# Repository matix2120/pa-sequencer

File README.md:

# pa-sequencer
Tiny board to key RF ampilifiers and LNAs

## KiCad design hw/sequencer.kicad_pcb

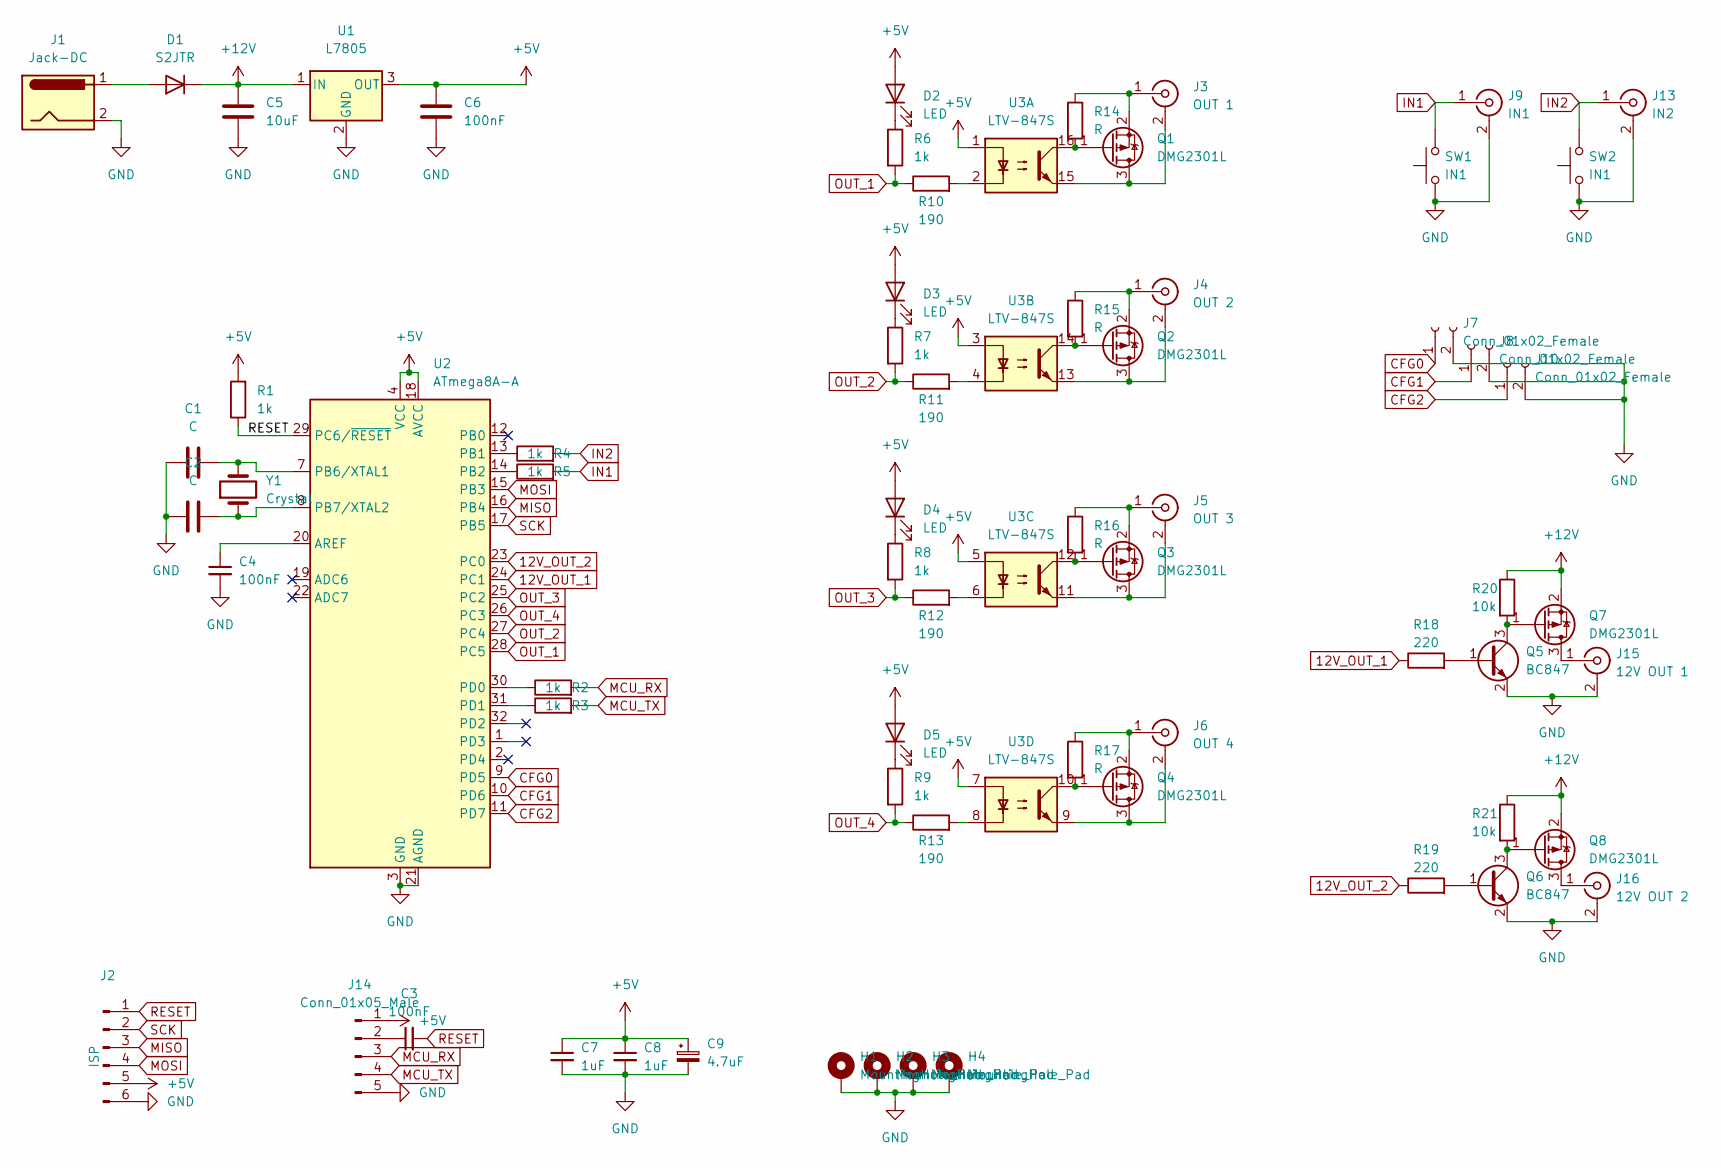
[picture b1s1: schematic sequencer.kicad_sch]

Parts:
C1, C2: C; C_0805_2012Metric_Pad1.18x1.45mm_HandSolder
C3, C4, C6: 100nF; C_0805_2012Metric_Pad1.18x1.45mm_HandSolder
C5: 10uF; C_0805_2012Metric_Pad1.18x1.45mm_HandSolder
C7, C8: 1uF; C_0805_2012Metric_Pad1.18x1.45mm_HandSolder
C9: 4.7uF; CP_Elec_4x4.5
D1: S2JTR; D_SMB
D2, D3, D4, D5: LED; LED_0805_2012Metric_Pad1.15x1.40mm_HandSolder
H1, H2, H3, H4: MountingHole_Pad; MountingHole_3.2mm_M3_Pad
J1: Jack-DC; PinHeader_1x02_P2.54mm_Vertical
J2: ISP; PinHeader_1x06_P2.54mm_Vertical
J3: OUT 1; PinHeader_1x02_P2.54mm_Vertical
J4: OUT 2; PinHeader_1x02_P2.54mm_Vertical
J5: OUT 3; PinHeader_1x02_P2.54mm_Vertical
J6: OUT 4; PinHeader_1x02_P2.54mm_Vertical
J7, J8, J10: Conn_01x02_Female; PinHeader_1x02_P2.54mm_Vertical
J9: IN1; PinHeader_1x02_P2.54mm_Vertical
J13: IN2; PinHeader_1x02_P2.54mm_Vertical
J14: Conn_01x05_Male; PinHeader_1x05_P2.54mm_Vertical
J15: 12V OUT 1; PinHeader_1x02_P2.54mm_Vertical
J16: 12V OUT 2; PinHeader_1x02_P2.54mm_Vertical
Q1, Q2, Q3, Q4, Q7, Q8: DMG2301L; SOT-23
Q5, Q6: BC847; SOT-23
R1, R2, R3, R4, R5, R6, R7, R8, R9: 1k; R_0805_2012Metric_Pad1.20x1.40mm_HandSolder
R10, R11, R12, R13: 190; R_0805_2012Metric_Pad1.20x1.40mm_HandSolder
R14, R15, R16, R17: R; R_0805_2012Metric_Pad1.20x1.40mm_HandSolder
R18, R19: 220; R_0805_2012Metric_Pad1.20x1.40mm_HandSolder
R20, R21: 10k; R_0805_2012Metric_Pad1.20x1.40mm_HandSolder
SW1, SW2: IN1; PTS636_SL43_SMTR_LFS
U1: L7805; TO-252-2
U2: ATmega8A-A; TQFP-32_7x7mm_P0.8mm
U3: LTV-847S; SMDIP-16_W9.53mm
Y1: Crystal; Crystal_SMD_HC49-SD

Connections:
12V_OUT_1: R18.1, U2.24 (PC1)
12V_OUT_2: R19.1, U2.23 (PC0)
+5V: C6.1, C7.1, C8.1, C9.1, D2.2 (A), D3.2 (A), D4.2 (A), D5.2 (A), J2.5, J14.1, R1.2, U1.3 (OUT), U2.4 (VCC), U2.6 (VCC), U2.18 (AVCC), U3.1, U3.3, U3.5, U3.7
+12V: C5.1, D1.1 (K), Q7.2 (S), Q8.2 (S), R20.1, R21.1, U1.1 (IN)
CFG0: J7.1, U2.9 (PD5)
CFG1: J8.1, U2.10 (PD6)
CFG2: J10.1, U2.11 (PD7)
GND: C1.2, C2.2, C4.2, C5.2, C6.2, C7.2, C8.2, C9.2, H1.1, H2.1, H3.1, H4.1, J1.2, J2.6, J7.2, J8.2, J9.2 (Ext), J10.2, J13.2 (Ext), J14.5, J15.2 (Ext), J16.2 (Ext), Q5.2 (E), Q6.2 (E), SW1.1, SW2.1, U1.2 (GND), U2.3 (GND), U2.5 (GND), U2.21 (AGND)
IN1: J9.1 (In), R5.2, SW1.2
IN2: J13.1 (In), R4.2, SW2.2
MCU_RX: J14.3, R2.2
MCU_TX: J14.4, R3.2
MISO: J2.3, U2.16 (PB4)
MOSI: J2.4, U2.15 (PB3)
unnamed: C1.1, U2.7 (PB6/XTAL1), Y1.2
unnamed: C2.1, U2.8 (PB7/XTAL2), Y1.1
unnamed: C4.1, U2.20 (AREF)
unnamed: D1.2 (A), J1.1
unnamed: D2.1 (K), R6.1
unnamed: D3.1 (K), R7.1
unnamed: D4.1 (K), R8.1
unnamed: D5.1 (K), R9.1
unnamed: J3.2 (Ext), Q1.3 (D), U3.15
unnamed: J4.1 (In), Q2.2 (S), R15.1
unnamed: J5.1 (In), Q3.2 (S), R16.1
unnamed: J6.1 (In), Q4.2 (S), R17.1
unnamed: C3.1, J14.2
unnamed: J15.1 (In), Q7.3 (D)
unnamed: J16.1 (In), Q8.3 (D)
unnamed: Q5.1 (B), R18.2
unnamed: Q5.3 (C), Q7.1 (G), R20.2
unnamed: Q6.1 (B), R19.2
unnamed: Q6.3 (C), Q8.1 (G), R21.2
unnamed: R2.1, U2.30 (PD0)
unnamed: R3.1, U2.31 (PD1)
unnamed: R10.2, U3.2
unnamed: R11.2, U3.4
unnamed: R12.2, U3.6
unnamed: R13.2, U3.8
unnamed: J3.1 (In), Q1.2 (S), R14.1
unnamed: Q1.1 (G), R14.2, U3.16
unnamed: R4.1, U2.13 (PB1)
unnamed: R5.1, U2.14 (PB2)
unnamed: J6.2 (Ext), Q4.3 (D), U3.9
unnamed: Q4.1 (G), R17.2, U3.10
unnamed: J5.2 (Ext), Q3.3 (D), U3.11
unnamed: Q3.1 (G), R16.2, U3.12
unnamed: J4.2 (Ext), Q2.3 (D), U3.13
unnamed: Q2.1 (G), R15.2, U3.14
OUT_1: R6.2, R10.1, U2.28 (PC5)
OUT_2: R7.2, R11.1, U2.27 (PC4)
OUT_3: R8.2, R12.1, U2.25 (PC2)
OUT_4: R9.2, R13.1, U2.26 (PC3)
RESET: C3.2, J2.1, R1.1, U2.29 (PC6/~RESET)
SCK: J2.2, U2.17 (PB5)

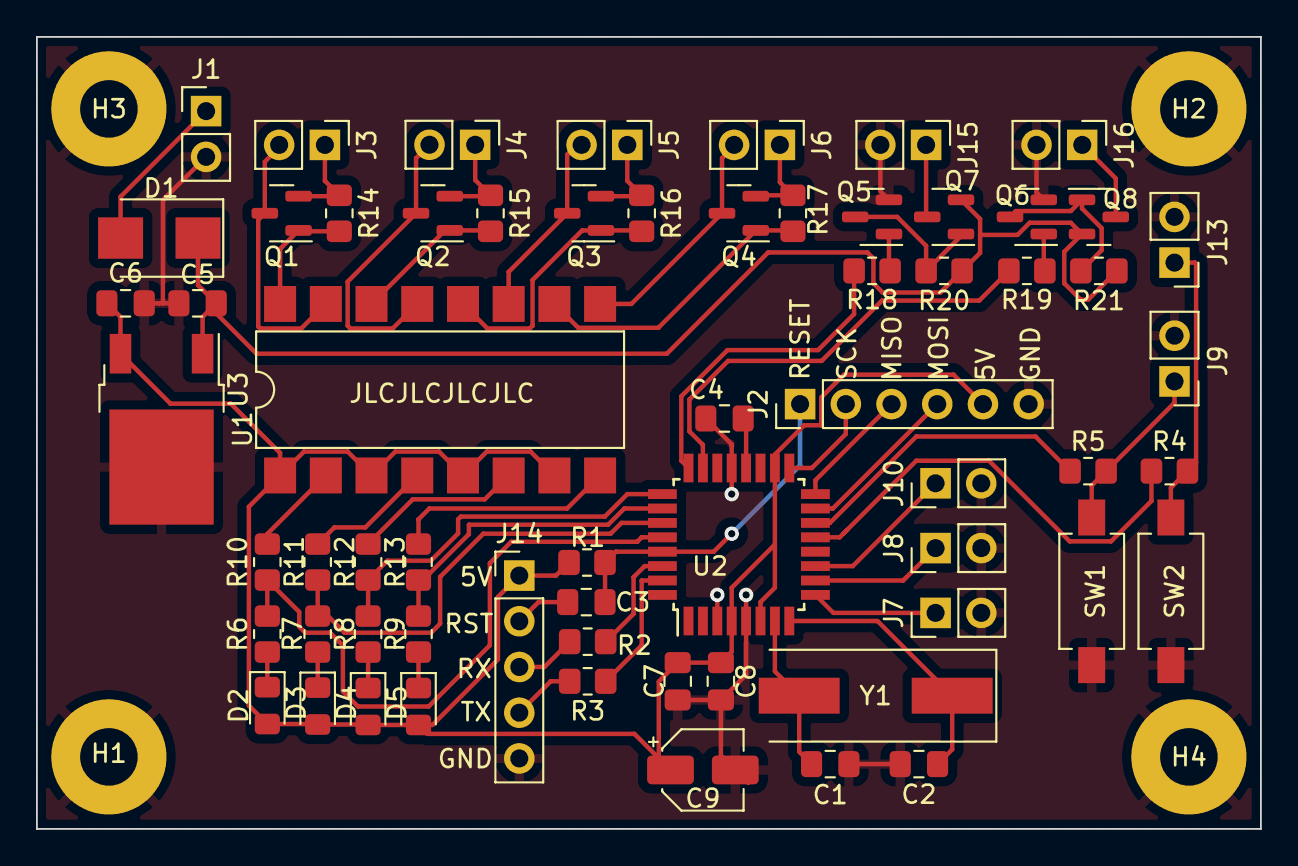
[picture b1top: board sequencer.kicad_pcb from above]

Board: 2 copper layers, 68.0 x 44.0 mm, 67 parts (0 on the bottom side), 55 nets.

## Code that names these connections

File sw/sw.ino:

#define IN1 PIN_PB2
#define IN2 PIN_PB1
#define OUT1 PIN_PC5
#define OUT2 PIN_PC4
#define OUT3 PIN_PC2
#define OUT4 PIN_PC3
#define OUT1_12V PIN_PC1
#define OUT2_12V PIN_PC0

#define OUT_ON(pin) digitalWrite(pin, LOW)
#define OUT_OFF(pin) digitalWrite(pin, HIGH)

#define OUT_12V_ON(pin) digitalWrite(pin, HIGH)
#define OUT_12V_OFF(pin) digitalWrite(pin, LOW)

#define PTT_ON(pin) !digitalRead(pin)

void setup() {
  Serial.begin(115200);
  Serial.println("PA Sequencer 2022");

  pinMode(IN1, INPUT_PULLUP);
  pinMode(IN2, INPUT_PULLUP);
  pinMode(OUT1, OUTPUT);
  pinMode(OUT2, OUTPUT);
  pinMode(OUT3, OUTPUT);
  pinMode(OUT4, OUTPUT);
  pinMode(OUT1_12V, OUTPUT);
  pinMode(OUT2_12V, OUTPUT);

  OUT_OFF(OUT1);
  OUT_OFF(OUT2);
  OUT_OFF(OUT3);
  OUT_OFF(OUT4);
  OUT_12V_OFF(OUT1_12V);
  OUT_12V_OFF(OUT2_12V);
}

void loop() {
  if(PTT_ON(IN1) || PTT_ON(IN2))
  {
    OUT_12V_OFF(OUT1_12V);
    OUT_12V_OFF(OUT2_12V);
    OUT_ON(OUT1);
    OUT_ON(OUT2);
    OUT_ON(OUT3);
    OUT_ON(OUT4);
  }
  else
  {
    OUT_12V_ON(OUT1_12V);
    OUT_12V_ON(OUT2_12V);
    OUT_OFF(OUT1);
    OUT_OFF(OUT2);
    OUT_OFF(OUT3);
    OUT_OFF(OUT4);
  }

//  Serial.print(digitalRead(OUT1));
//  Serial.print(",");
//  Serial.print(digitalRead(OUT2));
//  Serial.print(",");
//  Serial.print(digitalRead(OUT3));
//  Serial.print(",");
//  Serial.print(digitalRead(OUT4));
//  Serial.print(",");
//  Serial.print(digitalRead(OUT1_12V));
//  Serial.print(",");
//  Serial.println(digitalRead(OUT2_12V));
//  delay(100);
}

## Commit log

2022-09-01 Add schematic, pcb and gerbers
2022-09-01 Add .gitignore
2022-09-01 Add initial software
    TODO: Check if CFG pins are needed
